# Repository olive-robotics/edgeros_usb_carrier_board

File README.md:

# Olive Robotics EdgeROS SOM01-X USB Carrier Board

## Overview

This repository contains the KiCad project files for a carrier board designed to interface with the Olive Robotics EdgeROS SOM01-X. The carrier board connects via the 2x18 pin connector on the EdgeROS and provides a USB 2.0 interface.

## Features

- 2x18 pin connector for interfacing with EdgeROS SOM01-X
- USB 2.0 interface
- Designed using KiCad

## Prerequisites

- KiCad 7.0.1 or higher
- Basic understanding of PCB design and electronics

## Getting Started

1. **Clone the Repository**: Clone or download this repository to your local machine.
2. **Open the Project**: Navigate to the directory where you cloned the repository and open the KiCad project file.
3. **Review the Schematic**: Open the schematic editor to review the connections.
4. **Inspect the Layout**: Open the PCB layout editor to review or modify the board layout.
5. **Generate Gerber Files**: Once you are satisfied with the design, generate the Gerber files for manufacturing.

## Usage

1. **Assembly**: Solder the 2x18 pin connector and the USB 2.0 interface components onto the carrier board.
2. **Connection**: Connect the carrier board to the EdgeROS SOM01-X using the 2x18 pin connector.
3. **Testing**: Power up the EdgeROS and connect a USB device to test the interface.

## Contributing

If you find any issues or have suggestions for improvements, feel free to open an issue or submit a pull request.

## License

This project is open-source and available under the MIT License. See the `LICENSE.md` file for more information.

## Contact

For any questions or inquiries, please contact Olive Robotics at [contact@olive-robotics.com](mailto:contact@olive-robotics.com).

---

Happy building! 🤖

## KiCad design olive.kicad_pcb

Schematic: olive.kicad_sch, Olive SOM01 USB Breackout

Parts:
C1, C3: 100nF; C_0402_1005Metric
C2: 100uF; CP_EIA-3528-21_Kemet-B
D1: LED; LED_0603_1608Metric
H1, H2, H3, H4: MountingHole_Pad; MountingHole_2.2mm_M2_ISO7380_Pad
J1: Conn_01x04_Male; Molex_PicoBlade_53261-0471_1x04-1MP_P1.25mm_Horizontal
J2: Conn_02x18_Odd_Even; PinHeader_2x18_P1.27mm_Vertical_SMD
R1: 1K; R_0402_1005Metric

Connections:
+3V3: J2.4
+5V: C1.1, C2.1, C3.1, D1.2 (A), J1.4, J2.2
/CAN_RX: J2.17
/CAN_ST: J2.3
/CAN_TX: J2.19
/I2C1_SCL: J2.15
/I2C1_SDA: J2.13
/I2C6_SCL: J2.16
/I2C6_SDA: J2.14
/OSD_ADC_0: J2.36
/OSD_ADC_1: J2.34
/OSD_ADC_2: J2.32
/OSD_ADC_3: J2.30
/OSD_ADC_4: J2.28
/OSD_ADC_5: J2.26
/OSD_ADC_6: J2.24
/OSD_ADC_7: J2.22
/OSD_PWM_0: J2.21
/OSD_PWM_1: J2.23
/OSD_PWM_2: J2.25
/OSD_PWM_3: J2.27
/OSD_PWM_4: J2.29
/OSD_PWM_5: J2.31
/OSD_PWM_6: J2.33
/OSD_PWM_7: J2.35
/SPI-CLK: J2.7
/SPI-MISO: J2.9
/SPI-MOSI: J2.11
/SPI-NSS: J2.5
/TTL_RXD: J2.18
/TTL_TXD: J2.20
/USB_OSD1_D_N: J1.3, J2.8
/USB_OSD1_D_P: J1.2, J2.6
/USB_OSD_D_N: J2.12
/USB_OSD_D_P: J2.10
GND: C1.2, C2.2, C3.2, H1.1, H2.1, H3.1, H4.1, J1.1, J2.1, R1.1
unnamed: D1.1 (K), R1.2

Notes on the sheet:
PWR LEDs
Note: 3.3v Max 1800mA +5.0v Max 2000mA
Olive Robotics SOM01-X EdgeROS SOM Platform (c) Copyright, Olive Robotics GmbH, 2021 - Dec. All Rights Reserved.
Screw Pads
Note: To control the PWM signals, use the following files in the Oive Robotics OLIX RT Linux Kernel. /sys/class/pwm/pwmchip4/pwm3/duty_cycle /sys/class/pwm/pwmchip4/pwm2/duty_cycle /sys/class/pwm/pwmchip4/pwm1/duty_cycle /sys/class/pwm/pwmchip4/pwm0/duty_cycle /sys/class/pwm/pwmchip0/pwm3/duty_cycl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
Note: To read the adc data, use the following files in the Oive Robotics OLIX RT Linux Kernel. /sys/bus/iio/devices/iio:device0/in_voltage1_raw /sys/bus/iio/devices/iio:device0/in_voltage2_raw /sys/bus/iio/devices/iio:device0/in_voltage4_raw /sys/bus/iio/devices/iio:device0/in_voltage5_raw /sys/bus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
Note: DO Not USE! USB_OSD_D_N & USB_OSD_D_P

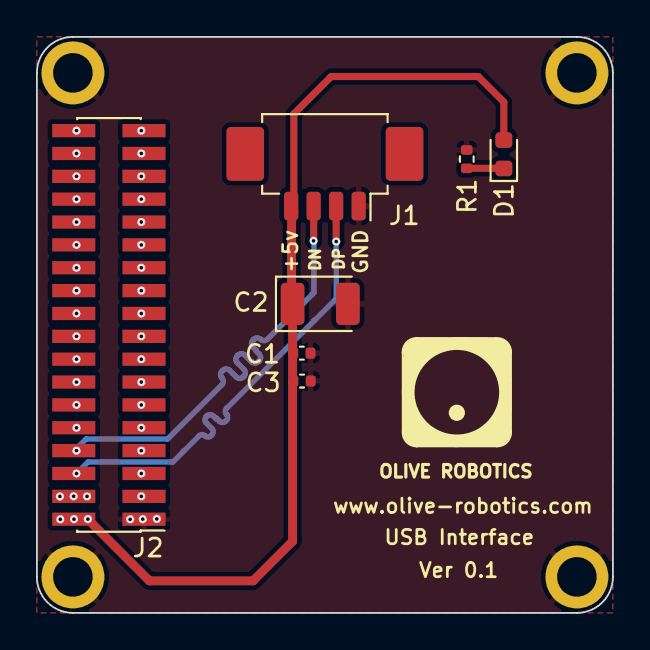
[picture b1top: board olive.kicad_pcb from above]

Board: 2 copper layers, 32.0 x 32.0 mm, 11 parts (0 on the bottom side), 5 nets.

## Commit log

2023-09-20 Initial Update
2024-01-27 Update README.md
    Adding 3D Images to the ReadMe
